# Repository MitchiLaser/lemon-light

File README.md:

# lemon-light
a couple of people trying to build a fancy monochrome LED display with bottles

## used bottles
We used lemonade bottles with 500 ml infill. The drinks boxes we bougth them inside had space for 26 bottles (4 x 6) and had a surface of 30cm x 40cm. Every box has its own controller which receives data via UART and drives the LEDs. The controllers can be connected in a dasy chain configuration.

## controllerboards

### slave

Every drink box has its own slave controller which is nothing more then an Attiny85 and 3 74hc595 shift registers. The Attiny receives the data via a UART interface, gets the first 3 bytes ans sends the rest to the next controller (also UART). Furthermore there is also an lm7805 attached because all boxes are powered via a voltage higher then 7,5V. This decision was made to prevent a voltage drop.

### master

The whole display is being controlled by a single master-controller which is made out of an ESP8266 and some electronics to translate the voltage for the serial interface between 3,3V and 5V. It is connected to a WiFi-interface and provides a web interface to control the boxes.

## 3D objects

There are some 3d printed objects that were used in the original build of this project: A part to hold the leds in the bottles and a box for the slave controller.

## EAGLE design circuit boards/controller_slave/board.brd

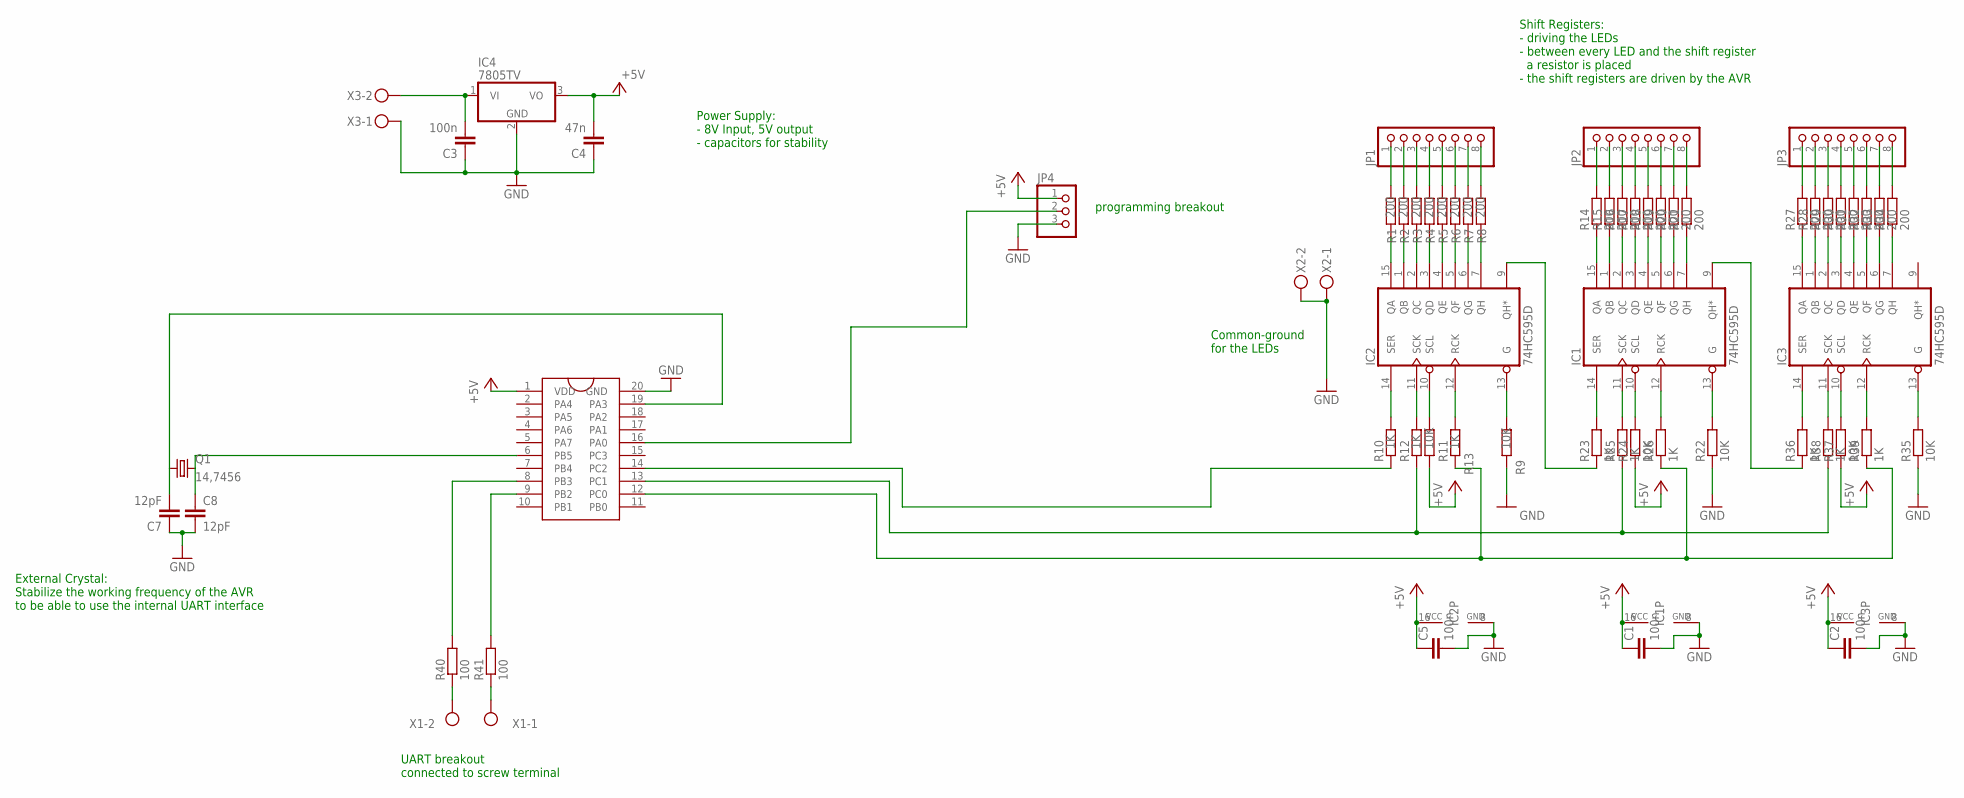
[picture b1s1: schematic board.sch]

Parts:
C1, C2, C3, C5: 100n; C0805K
C4: 47n; C0805K
C7, C8: 12pF; C0805K
IC1, IC2, IC3: 74HC595D; SO16
IC4: 7805TV; TO220V
JP1, JP2, JP3: PINHD-1X8; 1X08
JP4: PINHD-1X3; 1X03
Q1: 14,7456; SM49
R1, R2, R3, R4, R5, R6, R7, R8, R14, R15, R16, R17, R18, R19, R20, R21, R27, R28, R29, R30, R31, R32, R33, R34: 200; M0805
R9, R11, R22, R24, R35, R37: 10K; M0805
R10, R12, R13, R23, R25, R26, R36, R38, R39: 1K; M0805
R40, R41: 100; M0805
U$1: ATTINY406; SO20L
X1, X2, X3: MKDSN1,5/2-5,08

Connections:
+5V: C1.1, C2.1, C4.2, C5.1, IC1.16 (VCC), IC2.16 (VCC), IC3.16 (VCC), IC4.3 (VO), JP4.1, R11.1, R24.1, R37.1, U$1.1 (VDD)
GND: C1.2, C2.2, C3.1, C4.1, C5.2, C7.1, C8.2, IC1.8 (GND), IC2.8 (GND), IC3.8 (GND), IC4.2 (GND), JP4.3, R9.1, R22.1, R35.1, U$1.20 (GND), X2.1, X2.2, X3.1
unnamed: IC2.15 (QA), R1.1
unnamed: IC2.1 (QB), R2.1
unnamed: IC2.2 (QC), R3.1
unnamed: IC2.3 (QD), R4.1
unnamed: IC2.4 (QE), R5.1
unnamed: IC2.5 (QF), R6.1
unnamed: IC2.6 (QG), R7.1
unnamed: IC2.7 (QH), R8.1
unnamed: IC2.13 (G), R9.2
unnamed: IC2.14 (SER), R10.2
unnamed: IC2.11 (SCK), R12.2
unnamed: IC2.10 (SCL), R11.2
unnamed: IC2.12 (RCK), R13.2
unnamed: JP1.1, R1.2
unnamed: JP1.2, R2.2
unnamed: JP1.3, R3.2
unnamed: JP1.4, R4.2
unnamed: JP1.5, R5.2
unnamed: JP1.6, R6.2
unnamed: JP1.7, R7.2
unnamed: JP1.8, R8.2
unnamed: IC1.15 (QA), R14.1
unnamed: IC1.1 (QB), R15.1
unnamed: IC1.2 (QC), R16.1
unnamed: IC1.3 (QD), R17.1
unnamed: IC1.4 (QE), R18.1
unnamed: IC1.5 (QF), R19.1
unnamed: IC1.6 (QG), R20.1
unnamed: IC1.7 (QH), R21.1
unnamed: IC1.13 (G), R22.2
unnamed: IC1.14 (SER), R23.2
unnamed: IC1.11 (SCK), R25.2
unnamed: IC1.10 (SCL), R24.2
unnamed: IC1.12 (RCK), R26.2
unnamed: JP2.1, R14.2
unnamed: JP2.2, R15.2
unnamed: JP2.3, R16.2
unnamed: JP2.4, R17.2
unnamed: JP2.5, R18.2
unnamed: JP2.6, R19.2
unnamed: JP2.7, R20.2
unnamed: JP2.8, R21.2
unnamed: IC3.15 (QA), R27.1
unnamed: IC3.1 (QB), R28.1
unnamed: IC3.2 (QC), R29.1
unnamed: IC3.3 (QD), R30.1
unnamed: IC3.4 (QE), R31.1
unnamed: IC3.5 (QF), R32.1
unnamed: IC3.6 (QG), R33.1
unnamed: IC3.7 (QH), R34.1
unnamed: IC3.13 (G), R35.2
unnamed: IC3.14 (SER), R36.2
unnamed: IC3.11 (SCK), R38.2
unnamed: IC3.10 (SCL), R37.2
unnamed: IC3.12 (RCK), R39.2
unnamed: JP3.1, R27.2
unnamed: JP3.2, R28.2
unnamed: JP3.3, R29.2
unnamed: JP3.4, R30.2
unnamed: JP3.5, R31.2
unnamed: JP3.6, R32.2
unnamed: JP3.7, R33.2
unnamed: JP3.8, R34.2
unnamed: IC2.9 (QH*), R23.1
unnamed: IC1.9 (QH*), R36.1
unnamed: R40.1, X1.2
unnamed: R12.1, R25.1, R38.1, U$1.13 (PC1)
unnamed: R13.1, R26.1, R39.1, U$1.12 (PC0)
unnamed: R40.2, U$1.8 (PB3)
unnamed: R41.2, U$1.9 (PB2)
unnamed: R41.1, X1.1
unnamed: C3.2, IC4.1 (VI), X3.2
unnamed: R10.1, U$1.14 (PC2)
unnamed: C7.2, Q1.1, U$1.19 (PA3)
unnamed: JP4.2, U$1.16 (PA0)
unnamed: C8.1, Q1.2, U$1.6 (PB5)

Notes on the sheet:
UART breakout connected to screw terminal
Power Supply: - 8V Input, 5V output - capacitors for stability
Shift Registers: - driving the LEDs - between every LED and the shift register a resistor is placed - the shift registers are driven by the AVR
External Crystal: Stabilize the working frequency of the AVR to be able to use the internal UART interface
Common-ground for the LEDs
programming breakout

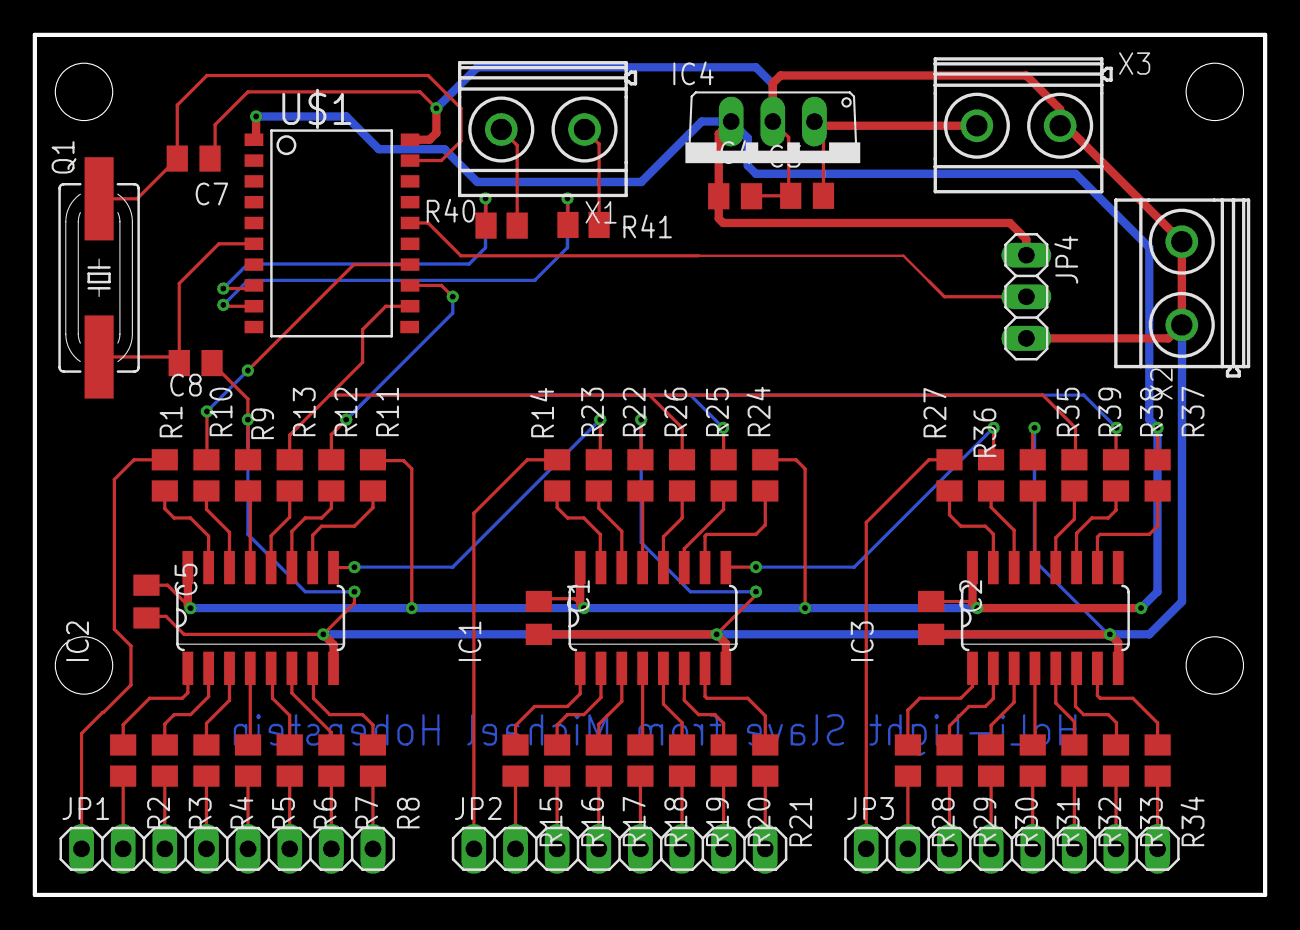
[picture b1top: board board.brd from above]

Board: 2 copper layers, 75.1 x 52.5 mm, 61 parts (0 on the bottom side), 78 nets.

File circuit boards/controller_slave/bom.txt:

Stückliste exportiert aus /home/michael/Dokumente/Freizeit-Projekte/lemon-light/circuit boards/controller_slave/board.sch am 19.10.21 02:42

Qty Value     Device          Package         Parts                                                                                                          Description                        CATEGORY  DESCRIPTION MANUFACTURER MF MPN      OC_FARNELL OC_NEWARK OPERATING_TEMP PART_STATUS POPULARITY ROHS_COMPLIANT SERIES SPICEPREFIX SUB-CATEGORY THERMALLOSS TYPE
1             10-XX           B3F-10XX        S1                                                                                                             OMRON SWITCH                                                             B3F-1000 176432     36M3542                              72                                                                        
3             MKDSN1,5/2-5,08 MKDSN1,5/2-5,08 X1, X2, X3                                                                                                     MKDSN 1,5/ 2-5,08 Printklemme                                                                                                     14                                                                        
1             PINHD-1X3       1X03            JP4                                                                                                            PIN HEADER                                                                                                                        92                                                                        
3             PINHD-1X8       1X08            JP1, JP2, JP3                                                                                                  PIN HEADER                         CONNECTOR                                                                                                                                   PIN-HEADER                   
2   100       R-EU_M0805      M0805           R40, R41                                                                                                       RESISTOR, European symbol                                                                                                                                                                                   
4   100n      C-EUC0805K      C0805K          C1, C2, C3, C5                                                                                                 CAPACITOR, European symbol                                                                                                        52                               C                                        
7   10K       R-EU_M0805      M0805           R9, R11, R22, R24, R35, R37, R43                                                                               RESISTOR, European symbol                                                                                                                                                                                   
2   12pF      C-EUC0805K      C0805K          C7, C8                                                                                                         CAPACITOR, European symbol                                                                                                        52                               C                                        
1   14,7456   CRYSTALSM49     SM49            Q1                                                                                                             CRYSTAL                                                                           unknown    unknown                              3                                                                         
10  1K        R-EU_M0805      M0805           R10, R12, R13, R23, R25, R26, R36, R38, R39, R42                                                               RESISTOR, European symbol                                                                                                                                                                                   
24  200       R-EU_M0805      M0805           R1, R2, R3, R4, R5, R6, R7, R8, R14, R15, R16, R17, R18, R19, R20, R21, R27, R28, R29, R30, R31, R32, R33, R34 RESISTOR, European symbol                                                                                                                                                                                   
1   4,7nF     C-EUC0805K      C0805K          C6                                                                                                             CAPACITOR, European symbol                                                                                                        52                               C                                        
1   47n       C-EUC0805K      C0805K          C4                                                                                                             CAPACITOR, European symbol                                                                                                        52                               C                                        
3   74HC595D  74HC595D        SO16            IC1, IC2, IC3                                                                                                  8-bit SHIFT REGISTER, output latch                                                                                                21                                                                        
1   7805TV    7805TV          TO220V          IC4                                                                                                            Positive VOLTAGE REGULATOR                                                                                                        57                                                                        
1   ATTINY406 ATTINY406       SO20L           U$1

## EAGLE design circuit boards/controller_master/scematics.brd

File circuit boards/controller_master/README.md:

Main Controller Design
===
- parts used
  - node MCU
  - small buck converter breakout board
  - SN74HCT245N (although a one channel version of it would be better)
  - screw terminals for power supply and TX
- design
  - soldered on a breadboard
  - the buck converter provides 5V power supply
  - the RX pin is shifted with the SN74HCT245N from the 3.3V to the 5V level
- notes
  - make sure not to pull the TX of the node MCU low during boot
    (if you use a different level shifter)
  - during boot some data is output which causes the display to show random stuff
    - could be avoided by connecting the output enable pin of the SN74HCT245N
      to some GPIO of the node mcu

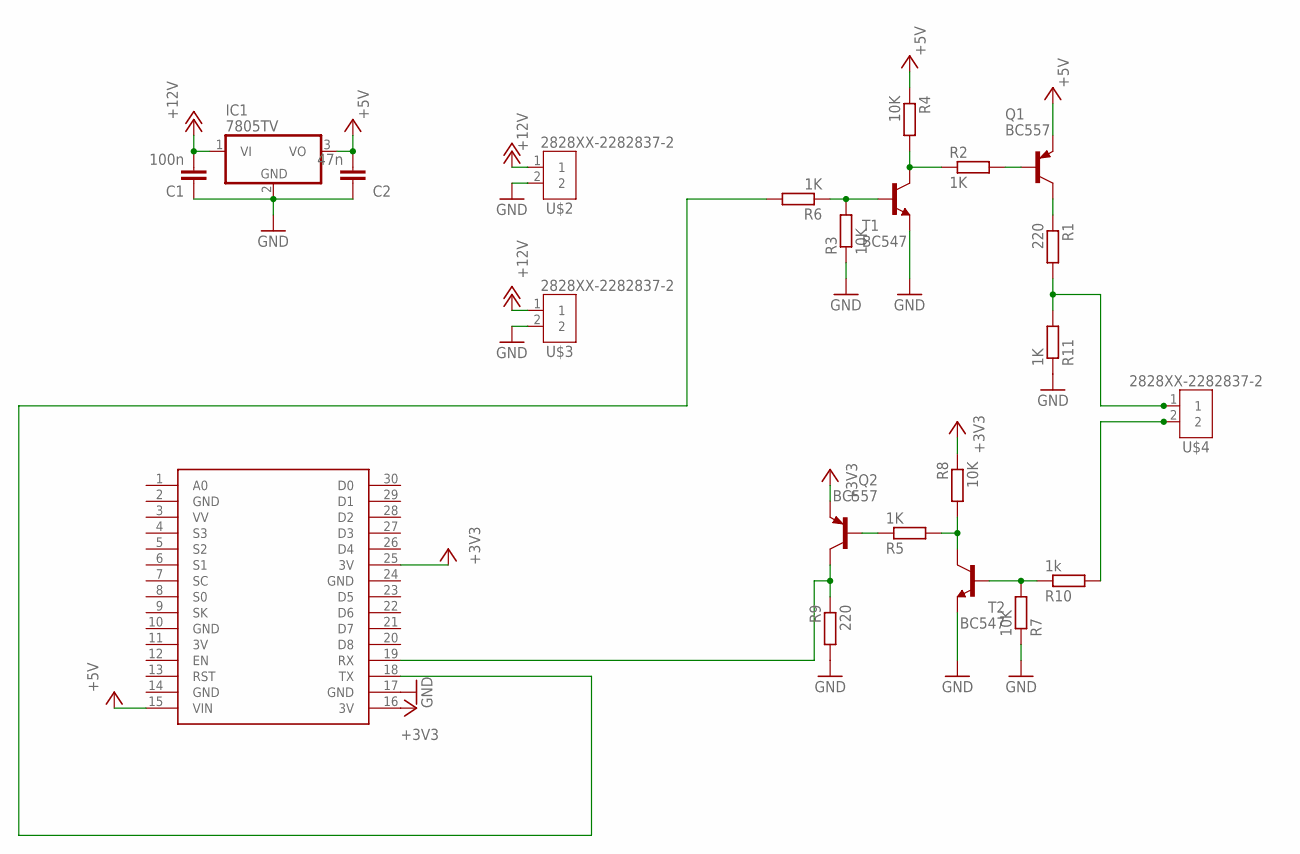
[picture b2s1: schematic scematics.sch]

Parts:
C1: 100n; C050-025X075
C2: 47n; C050-025X075
IC1: 7805TV; TO220V
Q1, Q2: BC557; TO92
R1, R9: 220; 0207/10
R2, R5, R6, R11: 1K; 0207/10
R3, R4, R7, R8: 10K; 0207/10
R10: 1k; 0207/10
T1, T2: BC547; TO92
U$1: NODEMCU
U$2, U$3, U$4: 2828XX-2282837-2; TERMBLK_508-2N

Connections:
3V: U$1.11 (3V)
+3V3: Q2.1 (E), R8.1, U$1.16 (3V), U$1.25 (3V)
+5V: C2.2, IC1.3 (VO), Q1.1 (E), R4.1, U$1.15 (VIN)
+12V: C1.2, IC1.1 (VI), U$2.1, U$3.1
GND: C1.1, C2.1, IC1.2 (GND), R3.1, R7.1, R9.2, R11.1, T1.1 (E), T2.1 (E), U$1.2 (GND), U$1.10 (GND), U$1.14 (GND), U$1.17 (GND), U$1.24 (GND), U$2.2, U$3.2
unnamed: Q1.2 (B), R2.2
unnamed: R3.2, R6.1, T1.2 (B)
unnamed: R2.1, R4.2, T1.3 (C)
unnamed: Q1.3 (C), R1.1
unnamed: Q2.2 (B), R5.1
unnamed: R7.2, R10.1, T2.2 (B)
unnamed: R5.2, R8.2, T2.3 (C)
unnamed: Q2.3 (C), R9.1, U$1.19 (RX)
unnamed: R10.2, U$4.2
unnamed: R1.2, R11.2, U$4.1
unnamed: R6.2, U$1.18 (TX)

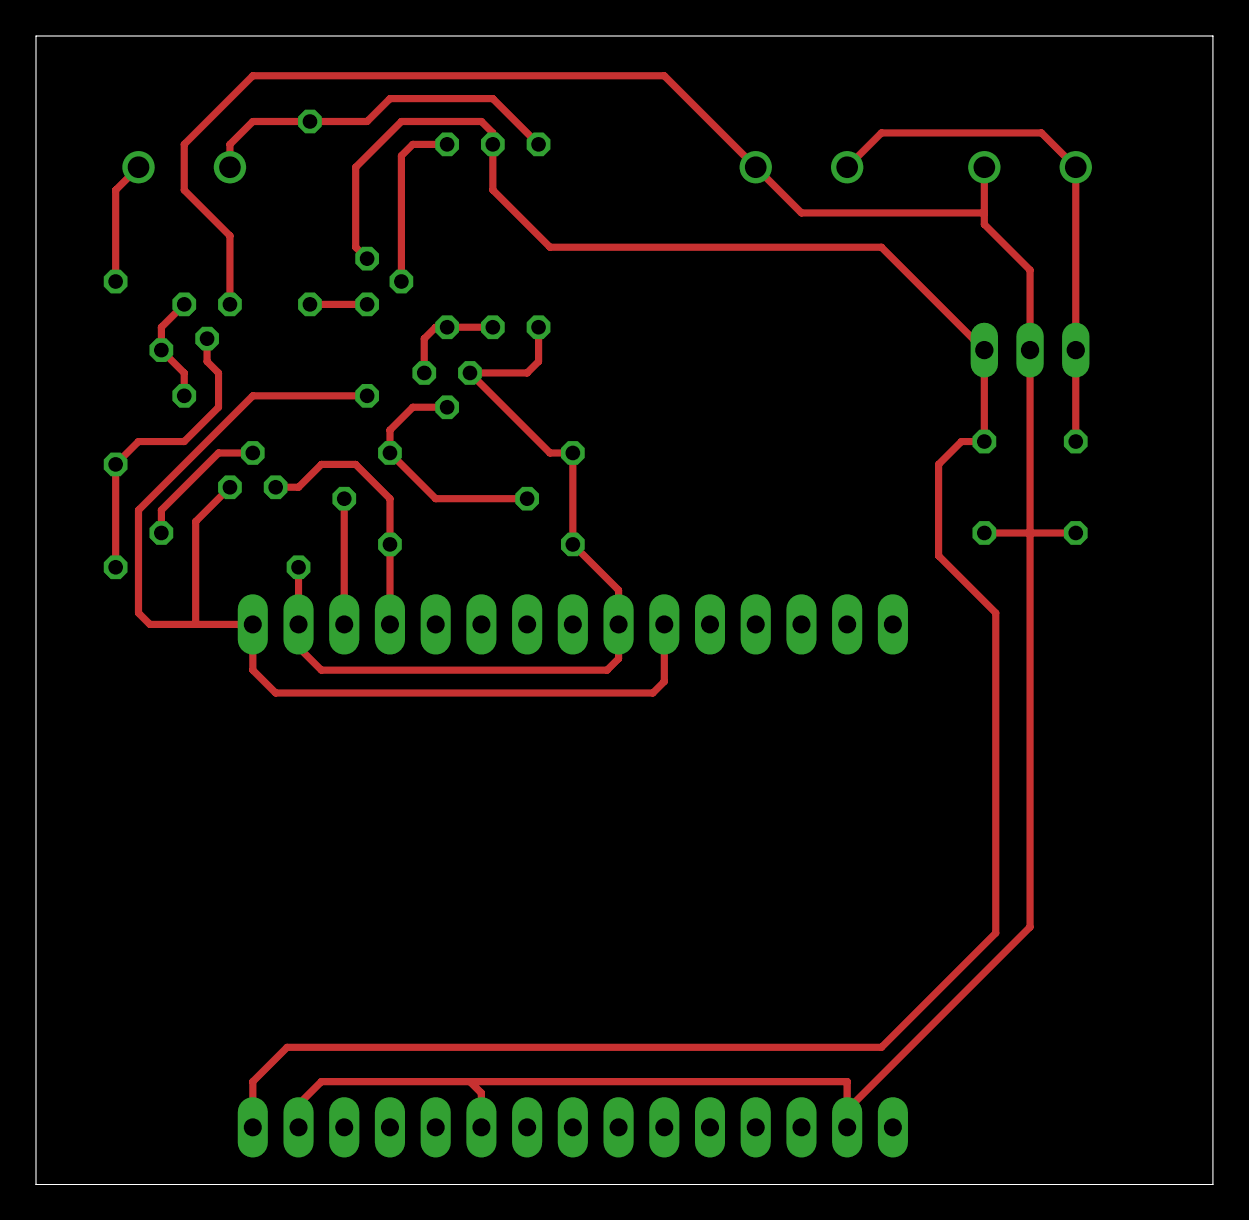
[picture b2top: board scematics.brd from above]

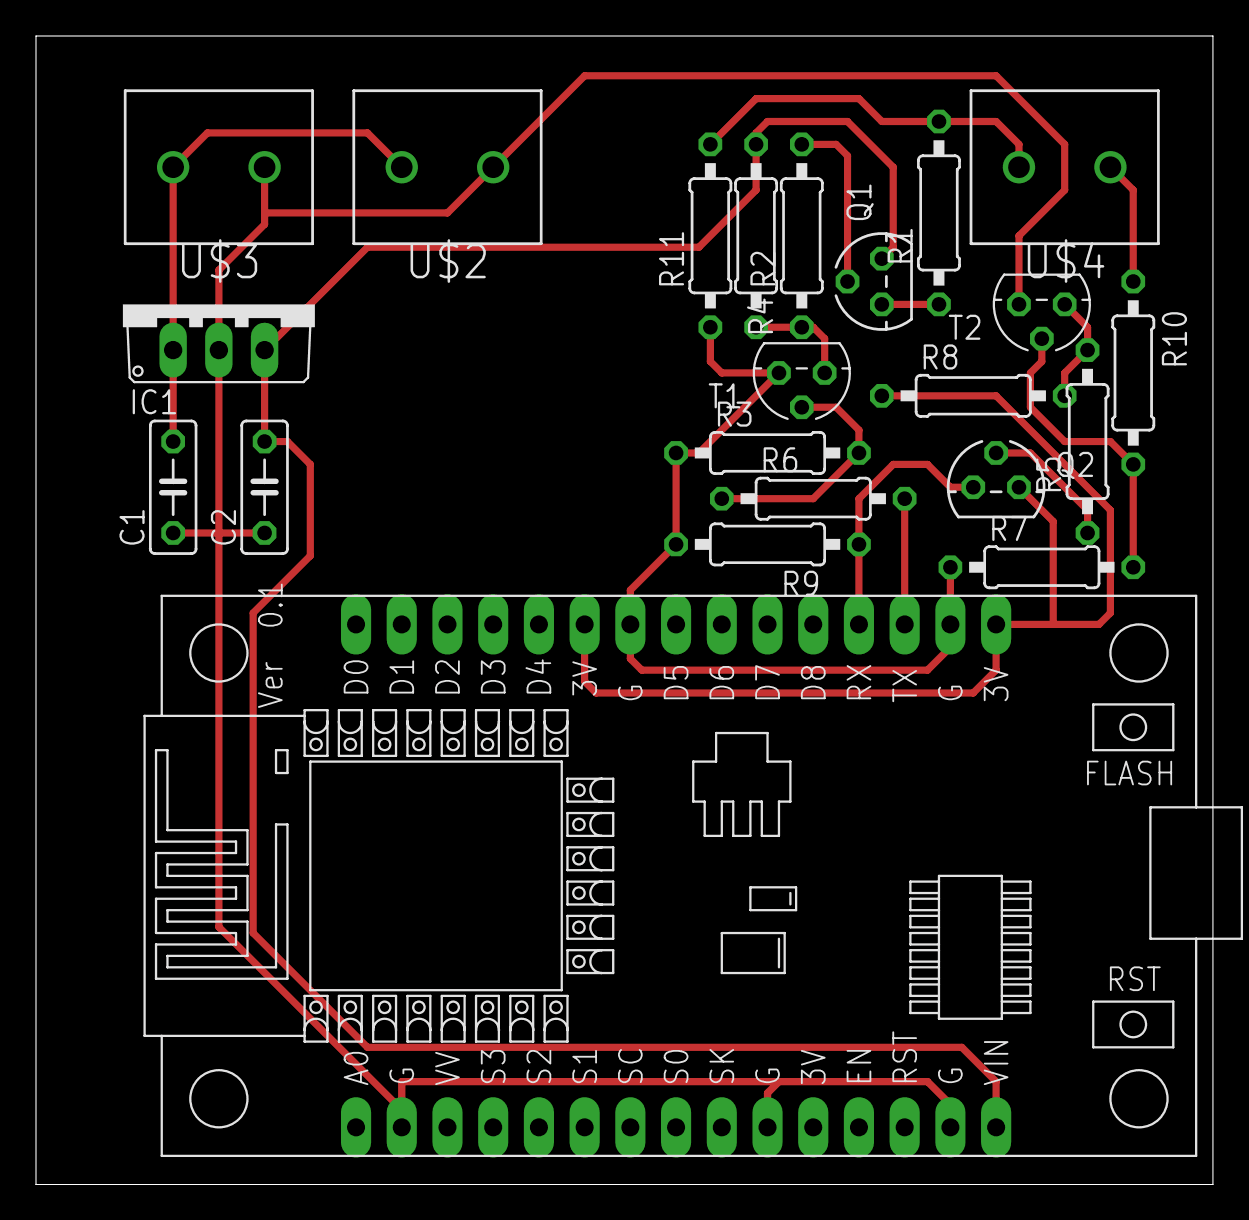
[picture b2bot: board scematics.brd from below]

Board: 2 copper layers, 65.4 x 63.8 mm, 22 parts (22 on the bottom side), 15 nets.

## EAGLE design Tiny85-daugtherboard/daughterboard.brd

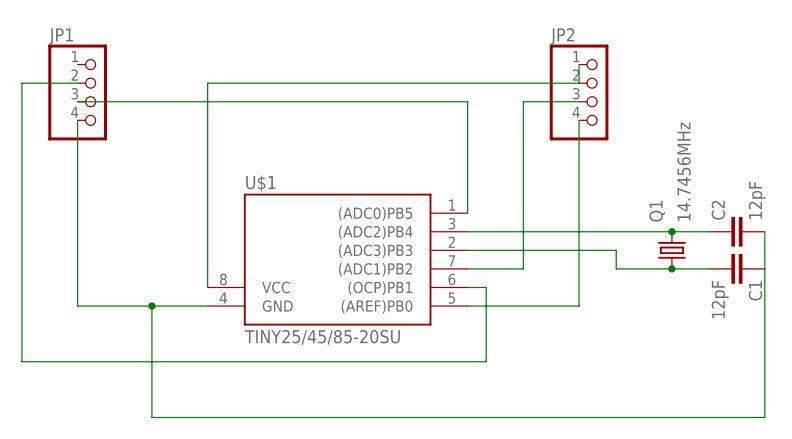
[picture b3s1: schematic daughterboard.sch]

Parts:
C1, C2: 12pF; C0805
JP1, JP2: PINHD-1X4; 1X04
Q1: 14.7456MHz; 3.2X2.5_KX-7
U$1: TINY25/45/85-20SU; SOIC8

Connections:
unnamed: JP2.1, JP2.2, U$1.8 (VCC)
unnamed: JP2.3, U$1.7 ((ADC1)PB2)
unnamed: JP2.4, U$1.5 ((AREF)PB0)
unnamed: C1.1, C2.2, JP1.4, U$1.4 (GND)
unnamed: JP1.3, U$1.1 ((ADC0)PB5)
unnamed: JP1.2, U$1.6 ((OCP)PB1)
unnamed: C2.1, Q1.3 (2), U$1.3 ((ADC2)PB4)
unnamed: C1.2, Q1.1, U$1.2 ((ADC3)PB3)

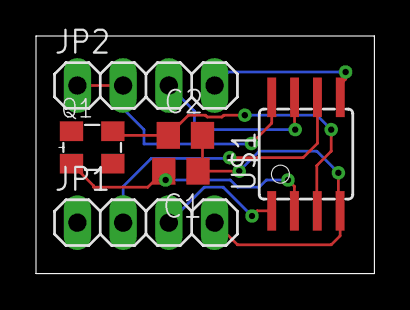
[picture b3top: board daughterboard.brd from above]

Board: 2 copper layers, 18.8 x 13.2 mm, 6 parts (0 on the bottom side), 8 nets.

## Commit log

2020-04-14 added Eagle scematic and pcb files for controller (slave)
2020-04-14 started developing firmware for the slaves
2021-01-01 prototype of firmware ready
2021-01-01 Update Readme and rename some folders
2021-01-01 fixed memory leak in buffer
2021-04-10 add 3D moddels off the LED Holders
2021-04-18 added code to test slave-controllers
2021-04-28 Design Controller Master
2021-04-28 cleaning up and adding some documentation
2021-05-18 added 3d model of the holder for the slave-controller circuit board inside the boxes
2021-05-18 fixed an issue with an unnecessary edge in the 3d objects
2021-06-02 Daughterboard und BSS-lib
2021-06-03 redesign slave pcb no daugtherboard needed
2021-06-03 update slave pcb: better connection to quarz
2021-06-03 Update documentation
2021-06-03 reorganised structure
2021-10-09 changed PCB: mostly SMD parts
2021-10-09 Controller Slave: Lastkapazität Quarz und UPDI Schnittstelle angepasst
2021-10-20 fixed minor issue: two power lanes were to close to each other
2022-01-22 removed reset circuit from board design
2022-01-22 Update Firmware, now working
2022-10-27 firmware for the display, now written with PlatformIO
2022-10-28 replace master controller board with description of breadboard design
2022-10-28 fix naming scheme
2022-10-28 deleted unused cage 3d object

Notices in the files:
parts and their libraries:
crystal-geyer_V1_0: Copyright: Geyer-Electronic
